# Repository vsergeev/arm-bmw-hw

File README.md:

# arm-bmw-hw

The ARM Bare Metal Widget (arm-bmw) is an open hardware Cortex-M0 development board with a focus on battery power, non-volatile storage, and debuggability. It is suitable as a battery-powered data logger or a general purpose embedded controller.

The arm-bmw features a small 70 x 43mm footprint, lithium polymer battery and USB power selection, a lithium polymer battery charger, a 2-megabyte Flash memory for data storage, a basic user interface, an FTDI-cable compatible UART header, JTAG-SWD for flashing and debugging, and 16 assorted I/O for connectivity. Its [BOM](#bill-of-materials) totals to under $15 USD. The arm-bmw is open hardware (CC-BY-4.0 licensed) and open source (MIT licensed).

Order 3 PCBs from [OSH Park](https://oshpark.com/) for $23.30 ($7.77 per board): <https://oshpark.com/shared_projects/iBdyoHro>

## Photos

## Specifications

* [NXP LPC1114FDH28](http://www.nxp.com/products/microcontrollers/cortex_m0_m0/lpc1100/LPC1114FDH28.html) 32-bit Cortex-M0 microcontroller
    * Up to 50MHz CPU
    * 12MHz on-chip RC oscillator
    * 32kB Flash, 8kB SRAM
    * 6-ch ADC, I2C, SPI, UART, PWM, Capture
* On-board 16-MBit (2-Mbyte) SPI Flash Memory (S25FL216K)
* Power
    * USB (mini-B connector) or LiPo Battery powered
    * 3-position power switch to select power between OFF, BAT, USB
    * On-board LiPo Battery Charger ([MCP73831T](http://www.microchip.com/wwwproducts/Devices.aspx?dDocName=en024903))
    * Power LED, Charge LED
* User Interface
    * On-board I2C I/O expander to save microcontroller I/Os ([MCP23008](http://www.microchip.com/wwwproducts/Devices.aspx?product=MCP23008))
    * 4 LEDs
    * 2 push buttons
    * 2 DIP switches
* Input/Output
    * 16-pin 0.1" pitch I/O header with I2C, SPI, Analog, Digital and Power pins
    * JTAG [Serial Wire Debug](http://www.arm.com/products/system-ip/debug-trace/coresight-soc-components/serial-wire-debug.php) header for Flashing and Debug
    * UART header, 6-pin [TTL-232R-3V3](http://www.ftdichip.com/Products/Cables/USBTTLSerial.htm) compatible
* Board
    * [Dangerous Prototypes SoB DP7043](http://dangerousprototypes.com/docs/Sick_of_Beige_standard_PCB_sizes_v1.0) (70x43mm / 2.756x1.693in) footprint
    * 4 mounting holes
* Miscellaneous
    * Optional external crystal and load capacitor pads
    * Hand-solderable packages

See the [datasheets](#datasheets) section below for links to part datasheets.

## Hardware Sources

Git: `git clone https://github.com/vsergeev/arm-bmw-hw.git`

GitHub: <https://github.com/vsergeev/arm-bmw-hw>

## Software Sources

Git: `git clone https://github.com/vsergeev/arm-bmw-sw.git`

GitHub: <https://github.com/vsergeev/arm-bmw-sw>

The arm-bmw-sw project includes a testing suite to verify the correct operation of the UART, SPI, I2C, SPI Flash, I/O Expander, LEDs, and Buttons.

## Details and Pinout

### Power and Charging

The arm-bmw provides a female JST-PH connector to accept a 3.7V lithium polymer battery, and a USB mini-B connector to accept 5V power from USB. The USB mini-B connector is only used for power and charging, not data.

A 3-position slide switch on the front selects between off, battery power, and USB power. The red Power LED indicates that 3.3V is present and that the arm-bmw is on. The orange Charge LED indicates that the lithium polymer battery is being charged from 5V USB power.

The onboard [MCP1252](http://www.microchip.com/wwwproducts/Devices.aspx?product=MCP1252) switched capacitor DC/DC converter regulates a 2V to 5.5V input to 3.3V, automatically switching between step down and step up operation as needed to provide 3.3V. This provides continuous power from a 3.7V lithium polymer battery as it drains to below 3.3V volts. The voltage regulator has a maximum output current of 120mA, so the arm-bmw should not be used to drive heavy loads alone.

The [MCP73831T](http://www.microchip.com/wwwproducts/Devices.aspx?dDocName=en024903) charge controller facilitates charging the connected lithium polymer battery. It operates whenever 5V power is present via the USB mini-B connector, regardless of the power slide switch state.

### Programming

The arm-bmw can be programmed and interactively debugged through its 5-pin JTAG-SWD header, with a SWD dongle like the [ST-LINK/V2](http://www.st.com/web/catalog/tools/FM146/CL1984/SC724/SS1677/PF251168?sc=internet/evalboard/product/251168.jsp). This dongle and the LPC1114 target are supported by [OpenOCD](http://openocd.sourceforge.net/). See [arm-bmw-sw](#software-sources) for configuration scripts for flashing and debugging over JTAG-SWD with openocd. See the JTAG-SWD header pinout [below](#jtag-swd-header-pinout).

The arm-bmw also supports programming over UART with its on-chip ROM bootloader. The 2-pin bootloader header on the front can be jumpered to start the on-chip ROM bootloader on reset. Software like [lpc21isp](http://sourceforge.net/projects/lpc21isp/) or [Flash Magic](http://www.flashmagictool.com/) can be used to program the LPC1114, over a UART-to-USB or UART-to-RS232 cable connected to the UART header. See the UART header pinout [below](#uart-header-pinout).

### SPI Flash Memory

The arm-bmw features a S25FL216K 16-MBit (2-MByte) SPI Flash for non-volatile storage in data logging applications. This SPI device is connected to the SPI0 controller of the microcontroller, sharing the MOSI, MISO, and SCK pins with the main [I/O header](#io-header-pinout). One microcontroller pin (`PIO0_2/SSEL0`) is dedicated to controlling its chip select.

### User Interface

The arm-bmw features a basic user interface, consisting of 4 LEDs, 2 push buttons, and 2 DIP switches. These 4 outputs and 4 inputs (8 I/Os total) are managed by an [MCP23008](http://www.microchip.com/wwwproducts/Devices.aspx?product=MCP23008) I2C I/O expander to conserve I/O pins on the microcontroller. The MCP23008 is connected to the I2C bus of the microcontroller, sharing the SDA and SCL pins with the main [I/O header](#io-header-pinout). In addition, one microcontroller pin (`PIO0_3`) is dedicated to the MCP23008 interrupt. The push buttons and DIP switches are debounced in hardware with an RC filter, to ensure that the MCP23008 interrupt is not spurious and to minimize the need for software debouncing.

The I2C address of the MCP23008 is configured by populating three 0-ohm jumpers on the back of the board, in either a 0 or 1 position, which pull down or up the MCP23008's A0, A1, A2 address pins. By default, these three jumpers are in the 0 position, so the MCP23008 has an address of `0x20` on the I2C bus.

Free software to drive the I2C bus, MCP23008 chip, and manage the UI is avaiable in the [arm-bmw-sw library](#software-sources).

### System Clock

The LPC1114 microcontroller has an on-chip 12MHz RC oscillator, which can be configured with the internal PLL to provide a 48MHz system clock using no external parts -- this is the default configuration. The arm-bmw also provides pads for an external HC49UP crystal and 0805 load capacitors for cases where a more accurate oscillator or a different multiple is required.

### I/O Header Pinout

The I/O header exposes one I2C bus (SDA, SCL), one SPI bus (MISO, MOSI, SCK), and 11 additional pins that may be used as digital I/O, ADC inputs, timer capture inputs, or PWM outputs, depending on the pin's supported functions.

| BMW Pin | uC Pin    | uC Pin Functions                  | Notes                             |
|:--------|:----------|:----------------------------------|:----------------------------------|
| `SDA`   | `PIO0_5`  | `PIO0_5/SDA`                      | I/O Expander shares this I2C bus. Pulled up with 10K. |
| `SCL`   | `PIO0_4`  | `PIO0_4/SCL`                      | I/O Expander shares this I2C bus. Pulled up with 10K. |
| `MISO`  | `PIO0_8`  | `PIO0_8/MISO0/CT16B0_MAT0`        | SPI Flash shares this SPI bus.    |
| `MOSI`  | `PIO0_9`  | `PIO0_9/MOSI0/CT16B0_MAT1`        | SPI Flash shares this SPI bus.    |
| `SCK`   | `PIO0_6`  | `PIO0_6/SCK0`                     | SPI Flash shares this SPI bus.    |
| `A0`    | `PIO0_11` | `PIO0_11/AD0/CT32B0_MAT3`         |                                   |
| `A1`    | `PIO1_0`  | `PIO1_0/AD1/CT32B1_CAP0`          |                                   |
| `A2`    | `PIO1_1`  | `PIO1_1/AD2/CT32B1_MAT0`          |                                   |
| `A3`    | `PIO1_2`  | `PIO1_2/AD3/CT32B1_MAT1`          |                                   |
| `A4`    | `PIO1_3`  | `SWDIO/PIO1_3/AD4/CT32B1_MAT2`    | JTAG-SWD header shares this pin.  |
| `A5`    | `PIO1_4`  | `PIO1_4/AD5/CT32B1_MAT3/WAKEUP`   |                                   |
| `P0`    | `PIO0_7`  | `PIO0_7/CTS`                      |                                   |
| `P1`    | `PIO0_10` | `SWCLK/PIO0_10/SCK0/CT16B0_MAT2`  | JTAG-SWD header shares this pin.  |
| `P2`    | `PIO1_5`  | `PIO1_5/RTS/CT32B0_CAP0`          |                                   |
| `P3`    | `PIO1_8`  | `PIO1_8/CT16B1_CAP0`              |                                   |
| `P4`    | `PIO1_9`  | `PIO1_9/CT16B1_MAT0`              |                                   |
| `3V3`   | -         | -                                 |                                   |
| `GND`   | -         | -                                 |                                   |

### JTAG-SWD Header Pinout

Compatible with [ST-LINK/V2](http://www.st.com/web/catalog/tools/FM146/CL1984/SC724/SS1677/PF251168?sc=internet/evalboard/product/251168.jsp) and other JTAG-SWD dongles.

| BMW Pin  | uC Pin    | uC Pin Functions                  | Notes                             |
|:---------|:----------|:----------------------------------|:----------------------------------|
| `!RST`   | `PIO0_0`  | `!RESET/PIO0_0`                   | Pulled up with 10K.               |
| `SWDIO`  | `PIO1_3`  | `SWDIO/PIO1_3/AD4/CT32B1_MAT2`    |                                   |
| `SWDCLK` | `PIO0_10` | `SWCLK/PIO0_10/SCK0/CT16B0_MAT2`  |                                   |
| `GND`    | -         | -                                 |                                   |
| `3V3`    | -         | -                                 |                                   |

### UART Header Pinout

Compatible with the [FTDI TTL-232R-3V3 cable](http://www.ftdichip.com/Products/Cables/USBTTLSerial.htm).

| BMW Pin | uC Pin   | uC Pin Functions                  | Notes                             |
|:--------|:---------|:----------------------------------|:----------------------------------|
| `GND`   | -        | -                                 |                                   |
| `NC`    | -        | -                                 |                                   |
| `NC`    | -        | -                                 |                                   |
| `uC RX` | `PIO1_6` | `PIO1_6/RXD/CT32B0_MAT0`          |                                   |
| `uC TX` | `PIO1_7` | `PIO1_7/TXD/CT32B0_MAT1`          |                                   |
| `NC`    | -        | -                                 |                                   |

## Schematic, Board, BOM

### Schematic

### Board Layout

### Bill of Materials

| Qty   | Part                                              | Description           | Part Number                       | Order Qty     | Total Price |
|:------|:--------------------------------------------------|:----------------------|:----------------------------------|:--------------|:------------|
| 1     | U1                                                | ARM Cortex-M0 MCU     | Arrow LPC1114FDH28/102:5          | 1             | 3.07        |
| 1     | U2                                                | SPI Flash Memory      | Digi-key 1274-1052-ND             | 1             | 0.32        |
| 1     | U3                                                | I2C I/O Expander      | Digi-key MCP23008-E/SO-ND         | 1             | 1.22        |
| 1     | U4                                                | 3.3V Regulator        | Digi-key MCP1252-33X50I/MS-ND     | 1             | 1.64        |
| 1     | U5                                                | LiPo Charger          | Digi-key MCP73831T-2ACI/OTCT-ND   | 1             | 0.67        |
| 8     | C3, C4, C5, C6, C10, C11, C13, C14                | C 0805 0.1uF          | Digi-key 1276-1099-1-ND           | 10            | 0.44        |
| 2     | C9, C12                                           | C 0805 1uF            | Digi-key 1276-1066-1-ND           | 5             | 0.50        |
| 2     | C15, C16                                          | C 0805 4.7uF          | Digi-key 1276-1244-1-ND           | 5             | 0.75        |
| 2     | C7, C8                                            | C 1206 10uF           | Digi-key 1276-1075-1-ND           | 5             | 1.15        |
| 8     | R1, R7, R8, R9, R14, R15, R16, R17, R18, R19, R27 | R 0805 10k            | Digi-key 1276-5332-1-ND           | 15            | 0.30        |
| 4     | R10, R11, R12, R13                                | R 0805 100k           | Digi-key 1276-3512-1-ND           | 10            | 0.20        |
| 6     | R20, R21, R22, R23, R24, R25                      | R 0603 0 jumper       | Digi-key RHM0.0CGCT-ND            | 10            | 0.10        |
| 4     | LED1, LED2, LED3, LED4                            | Green LED             | Digi-key 475-1410-1-ND            | 5             | 0.40        |
| 1     | LED_PWR                                           | Red LED               | Digi-key 475-1415-1-ND            | 2             | 0.16        |
| 1     | LED_CHG                                           | Orange LED            | Digi-key 754-1130-1-ND            | 2             | 0.40        |
| 5     | R2, R3, R4, R5, R6, R26                           | R 0805 for LED 1.5k   | Digi-key 1276-5533-1-ND           | 10            | 0.18        |
| 1     | CON_BAT                                           | JST-PH Connector      | Digi-key 455-1749-1-ND            | 1             | 0.56        |
| 1     | CON_USB                                           | USB Mini-B Connector  | Digi-key 151-1206-1-ND            | 1             | 0.41        |
| 1     | JP_*,TP_*                                         | 40p header break-away | Digi-key S1012EC-30-ND            | 1             | 0.48        |
| 1     | JP_UART                                           | 6p header right angle | Digi-key S1112EC-06-ND            | 1             | 0.23        |
| 1     | SW_PWR                                            | Slide switch          | Digi-key 563-1095-1-ND            | 1             | 0.63        |
| 2     | SW_B0, SW_B1                                      | Tactile switch        | Digi-key 450-1792-1-ND            | 2             | 0.40        |
| 1     | SW_DIP                                            | 2-pos DIP switch      | Digi-key 450-2045-ND              | 1             | 0.81        |
| 1 OPT | BATTERY                                           | 3.7V LiPo Battery     | SparkFun [PRT-00731](https://www.sparkfun.com/products/731) | 1 | 4.95 |
| 4 OPT | STANDOFF                                          | 10mm Nylon Standoff   | Digi-key 25510K-ND                | 4             | 2.36        |
| 4 OPT | STANDOFF SCREW                                    | 7mm Nylon Screw       | Digi-key 29341K-ND                | 4             | 0.76        |
| DNP   | C1, C2                                            | C 0805 xtal load caps | -                                 | -             | -           |
| DNP   | Q1                                                | Crystal               | -                                 | -             | -           |
|       | **Parts Total**                                   |                       |                                   |               | **$15.02**  |

The parts total does not include the PCB, LiPo battery, or standoffs.

Order 3 PCBs from [OSH Park](https://oshpark.com/) for $23.30 ($7.77 per board): <https://oshpark.com/shared_projects/iBdyoHro>

The unit price of a complete arm-bmw comes out to $22.79, with the BOM parts above and PCBs from OSH Park.

## Datasheets

* U1, ARM Cortex-M0 MCU, LPC1114FDH28: [site](http://www.nxp.com/products/microcontrollers/cortex_m0_m0/lpc1100/LPC1114FDH28.html), [datasheet](http://www.nxp.com/documents/data_sheet/LPC111X.pdf), [user manual](http://www.nxp.com/documents/user_manual/UM10398.pdf)
* U2, SPI Flash Memory, S25FL216K: [datasheet](http://www.spansion.com/Support/Datasheets/S25FL216K_00.pdf)
* U3, I2C I/O Expander, MCP23008: [site](http://www.microchip.com/wwwproducts/Devices.aspx?product=MCP23008), [datasheet](http://ww1.microchip.com/downloads/en/DeviceDoc/21919e.pdf)
* U4, 3.3V DC/DC Converter, MCP1252: [site](http://www.microchip.com/wwwproducts/Devices.aspx?product=MCP1252), [datasheet](http://ww1.microchip.com/downloads/en/DeviceDoc/21752B.pdf)
* U5, LiPo Charge Controller, MCP73831T: [site](http://www.microchip.com/wwwproducts/Devices.aspx?dDocName=en024903), [datasheet](http://ww1.microchip.com/downloads/en/DeviceDoc/20001984g.pdf)

## Change Log

* **Revision 2 - 06/06/2014**
    * Schematic
        * Add Dangerous Prototypes DP7043 pcb footprint and mounting holes
        * Add lipo battery charger and charge status led
        * Add mini-b usb connector for charging or usb power
        * Add capacitors for hardware debouncing for 2 pos dip switch
        * Change all 0603 size components to 0805 size
        * Change C12 size to 0805 (same as C9)
        * Change 0402 size for I2C IO expander address jumpers to 0603 size
        * Change I2C pull-ups to 10k
        * Change BL bootloader switch to a pin header jumper
        * Change test points to single pin headers
    * Layout
        * Change to longer pads on io expander
        * Change to longer pads on voltage regulator
        * Change test point pin headers to 0.1" pitch apart
        * Move passives away from I2C IO expander for easier soldering
        * Move passives away from voltage regulator for easier soldering
        * Label the UART header pins
    * BOM
        * Change power switch from mom-on-mom to on-on-on
        * Change spi flash size from 8mbit to 16mbit (same price)
        * Change to taller 2-pos DIP switch
* Revision 1 - 09/16/2013
    * Initial release

## License

arm-bmw-hw is [CC-BY-4.0](https://creativecommons.org/licenses/by/4.0/) licensed.

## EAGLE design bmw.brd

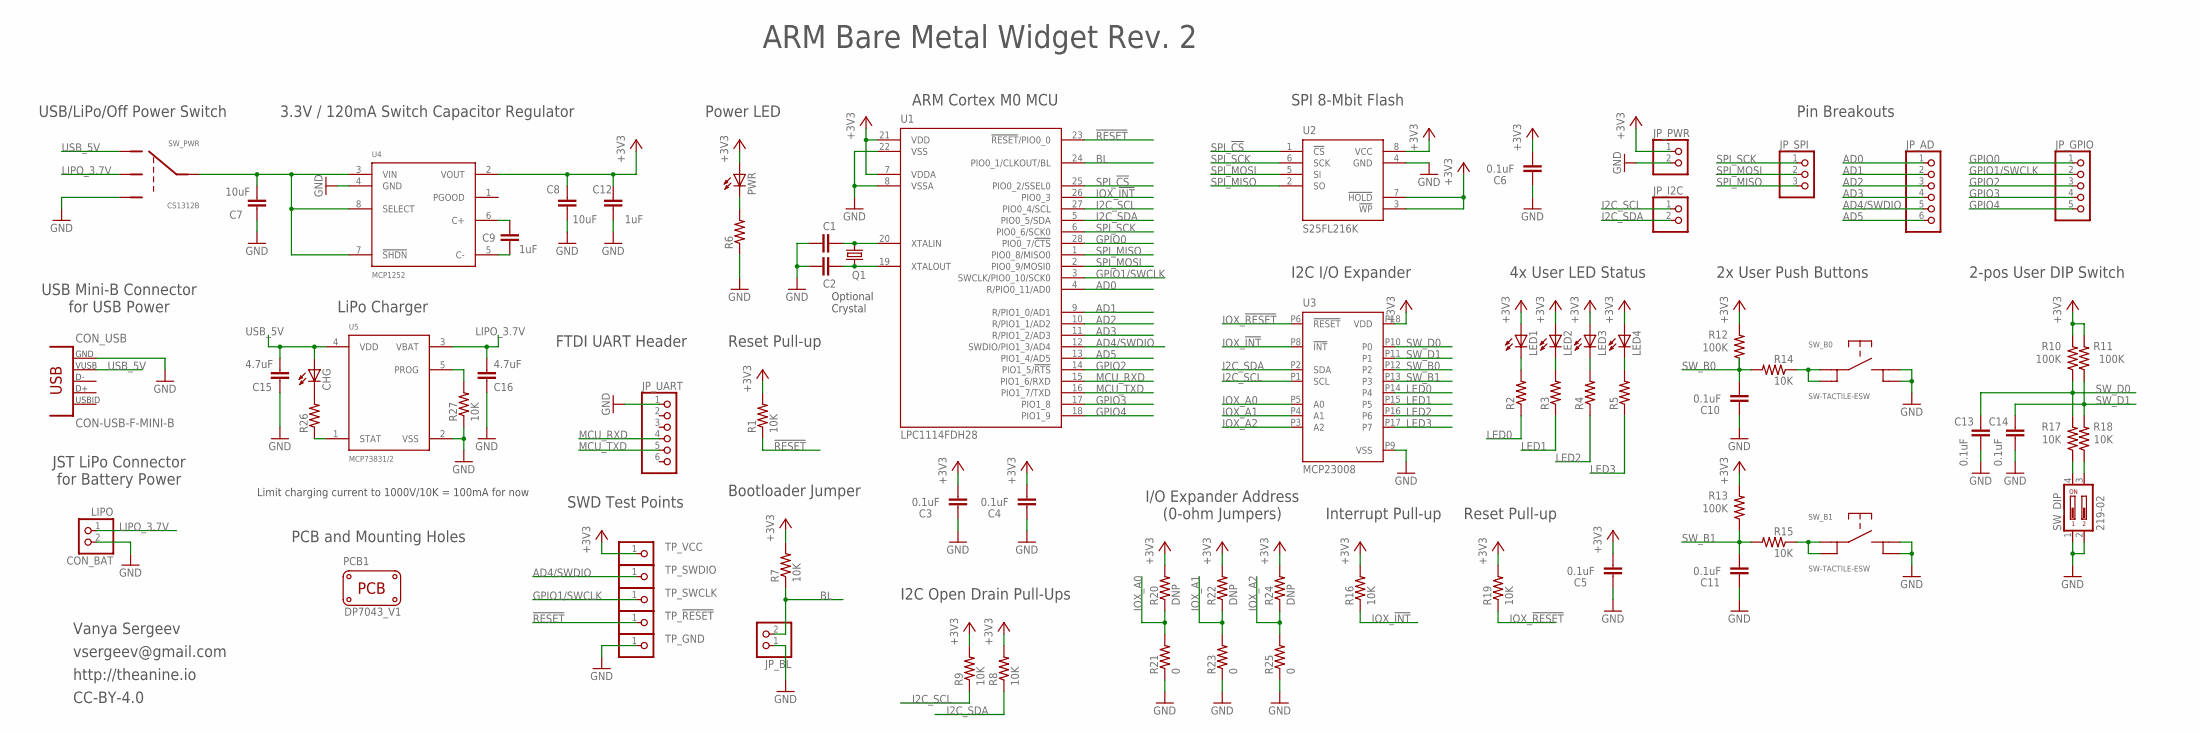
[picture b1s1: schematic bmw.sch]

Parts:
C1, C2: C-EUC0805; C0805
C3, C4, C5, C6, C10, C11, C13, C14: 0.1uF; C0805
C7, C8: 10uF; C1206
C9, C12: 1uF; C0805
C15, C16: 4.7uF; C0805
CHG: LEDCHIPLED_0805; CHIPLED_0805
CON_BAT: LIPO; JST-PH-2-SMT-RA
CON_USB: CON-USB-F-MINI-B; CONN_USB_MINI-B
JP_AD: PINHD-1X6; 1X06
JP_BL: PINHD-1X2; 1X02
JP_GPIO: PINHD-1X5; 1X05
JP_I2C: PINHD-1X2; 1X02
JP_PWR: PINHD-1X2; 1X02
JP_SPI: PINHD-1X3; 1X03
JP_UART: PINHD-1X6/90; 1X06/90
LED1, LED2, LED3, LED4: LEDCHIPLED_0805; CHIPLED_0805
PCB1: PCB_DP_RECTANGLE-43X70; DP7043_V1
PWR: LEDCHIPLED_0805; CHIPLED_0805
Q1: CRYSTALHC49UP; HC49UP
R1, R7, R8, R9, R14, R15, R16, R17, R18, R19, R27: 10K; R0805
R2, R3, R4, R5, R6, R26: R-US_R0805; R0805
R10, R11, R12, R13: 100K; R0805
R20, R22, R24: DNP; R0603
R21, R23, R25: 0; R0603
SW_B0, SW_B1: SW-TACTILE-ESW; SW-TACT-ESW
SW_DIP: 219-02; CTS-219-02
SW_PWR: CS1312B
TP_!RESET: PINHD-1X1; 1X01
TP_GND: PINHD-1X1; 1X01
TP_SWCLK: PINHD-1X1; 1X01
TP_SWDIO: PINHD-1X1; 1X01
TP_VCC: PINHD-1X1; 1X01
U1: LPC1114FDH28; TSSOP28
U2: S25FL216K; SOIC127P600X175-8N
U3: MCP23008; SOIC-18W
U4: MCP1252; MSOP8
U5: MCP73831/2; SOT23-5L

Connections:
!RESET!: R1.1, TP_!RESET.1, U1.23 (!RESET!/PIO0_0)
+3V3: C3.2, C4.2, C5.2, C6.2, C8.2, C12.2, JP_PWR.1, LED1.A, LED2.A, LED3.A, LED4.A, PWR.A, R1.2, R7.2, R8.2, R9.2, R10.2, R11.2, R12.2, R13.2, R16.2, R19.2, R20.2, R22.2, R24.2, TP_VCC.1, U1.7 (VDDA), U1.21 (VDD), U2.3 (!WP!), U2.7 (!HOLD!), U2.8 (VCC), U3.P18 (VDD), U4.2 (VOUT)
AD0: JP_AD.1, U1.4 (R/PIO0_11/AD0)
AD1: JP_AD.2, U1.9 (R/PIO1_0/AD1)
AD2: JP_AD.3, U1.10 (R/PIO1_1/AD2)
AD3: JP_AD.4, U1.11 (R/PIO1_2/AD3)
AD4/SWDIO: JP_AD.5, TP_SWDIO.1, U1.12 (SWDIO/PIO1_3/AD4)
AD5: JP_AD.6, U1.13 (PIO1_4/AD5)
BL: JP_BL.2, R7.1, U1.24 (PIO0_1/CLKOUT/BL)
GND: C1.1, C2.1, C3.1, C4.1, C5.1, C6.1, C7.1, C8.1, C10.1, C11.1, C12.1, C13.2, C14.2, C15.1, C16.1, CON_BAT.2 (1), CON_USB.GND, JP_BL.1, JP_PWR.2, JP_UART.1, R6.1, R21.1, R23.1, R25.1, R27.1, SW_B0.P3, SW_B0.P4, SW_B1.P3, SW_B1.P4, SW_DIP.1, SW_DIP.2, SW_PWR.P4 (3), TP_GND.1, U1.8 (VSSA), U1.22 (VSS), U2.4 (GND), U3.P9 (VSS), U4.4 (GND), U5.2 (VSS)
GPIO0: JP_GPIO.1, U1.28 (PIO0_7/!CTS!)
GPIO1/SWCLK: JP_GPIO.2, TP_SWCLK.1, U1.3 (SWCLK/PIO0_10/SCK0)
GPIO2: JP_GPIO.3, U1.14 (PIO1_5/!RTS!)
GPIO3: JP_GPIO.4, U1.17 (PIO1_8)
GPIO4: JP_GPIO.5, U1.18 (PIO1_9)
I2C_SCL: JP_I2C.1, R9.1, U1.27 (PIO0_4/SCL), U3.P1 (SCL)
I2C_SDA: JP_I2C.2, R8.1, U1.5 (PIO0_5/SDA), U3.P2 (SDA)
IOX_!INT: R16.1, U1.26 (PIO0_3), U3.P8 (!INT)
IOX_!RESET: R19.1, U3.P6 (!RESET)
IOX_A0: R20.1, R21.2, U3.P5 (A0)
IOX_A1: R22.1, R23.2, U3.P4 (A1)
IOX_A2: R24.1, R25.2, U3.P3 (A2)
LED0: R2.1, U3.P14 (P4)
LED1: R3.1, U3.P15 (P5)
LED2: R4.1, U3.P16 (P6)
LED3: R5.1, U3.P17 (P7)
LIPO_3.7V: C16.2, CON_BAT.1 (2), SW_PWR.P2 (2), U5.3 (VBAT)
MCU_RXD: JP_UART.4, U1.15 (PIO1_6/RXD)
MCU_TXD: JP_UART.5, U1.16 (PIO1_7/TXD)
unnamed: R17.1, SW_DIP.4
unnamed: C1.2, Q1.2, U1.20 (XTALIN)
unnamed: C2.2, Q1.1, U1.19 (XTALOUT)
unnamed: PWR.C, R6.2
unnamed: C7.2, SW_PWR.P3 (C), U4.3 (VIN), U4.7 (!SHDN), U4.8 (SELECT)
unnamed: C9.2, U4.6 (C+)
unnamed: C9.1, U4.5 (C-)
unnamed: LED1.C, R2.2
unnamed: LED2.C, R3.2
unnamed: LED3.C, R4.2
unnamed: LED4.C, R5.2
unnamed: R14.1, SW_B0.P1, SW_B0.P2
unnamed: R15.1, SW_B1.P1, SW_B1.P2
unnamed: R18.1, SW_DIP.3
unnamed: CHG.C, R26.2
unnamed: R26.1, U5.1 (STAT)
unnamed: R27.2, U5.5 (PROG)
SPI_!CS!: U1.25 (PIO0_2/SSEL0), U2.1 (!CS!)
SPI_MISO: JP_SPI.3, U1.1 (PIO0_8/MISO0), U2.2 (SO)
SPI_MOSI: JP_SPI.2, U1.2 (PIO0_9/MOSI0), U2.5 (SI)
SPI_SCK: JP_SPI.1, U1.6 (PIO0_6/SCK0), U2.6 (SCK)
SW_B0: C10.2, R12.1, R14.2, U3.P12 (P2)
SW_B1: C11.2, R13.1, R15.2, U3.P13 (P3)
SW_D0: C13.1, R10.1, R17.2, U3.P10 (P0)
SW_D1: C14.1, R11.1, R18.2, U3.P11 (P1)
USB_5V: C15.2, CHG.A, CON_USB.VUSB, SW_PWR.P1 (1), U5.4 (VDD)

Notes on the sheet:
I2C I/O Expander
SPI 8-Mbit Flash
ARM Cortex M0 MCU
Reset Pull-up
4x User LED Status
2x User Push Buttons
2-pos User DIP Switch
SWD Test Points
FTDI UART Header
Bootloader Jumper
Power LED
I2C Open Drain Pull-Ups
3.3V / 120mA Switch Capacitor Regulator
USB/LiPo/Off Power Switch
ARM Bare Metal Widget Rev. 2
Vanya Sergeev
vsergeev@gmail.com
http://theanine.io
Pin Breakouts
Optional Crystal
Interrupt Pull-up
I/O Expander Address (0-ohm Jumpers)
PCB and Mounting Holes
LiPo Charger
Limit charging current to 1000V/10K = 100mA for now
USB Mini-B Connector for USB Power
JST LiPo Connector for Battery Power
CC-BY-4.0

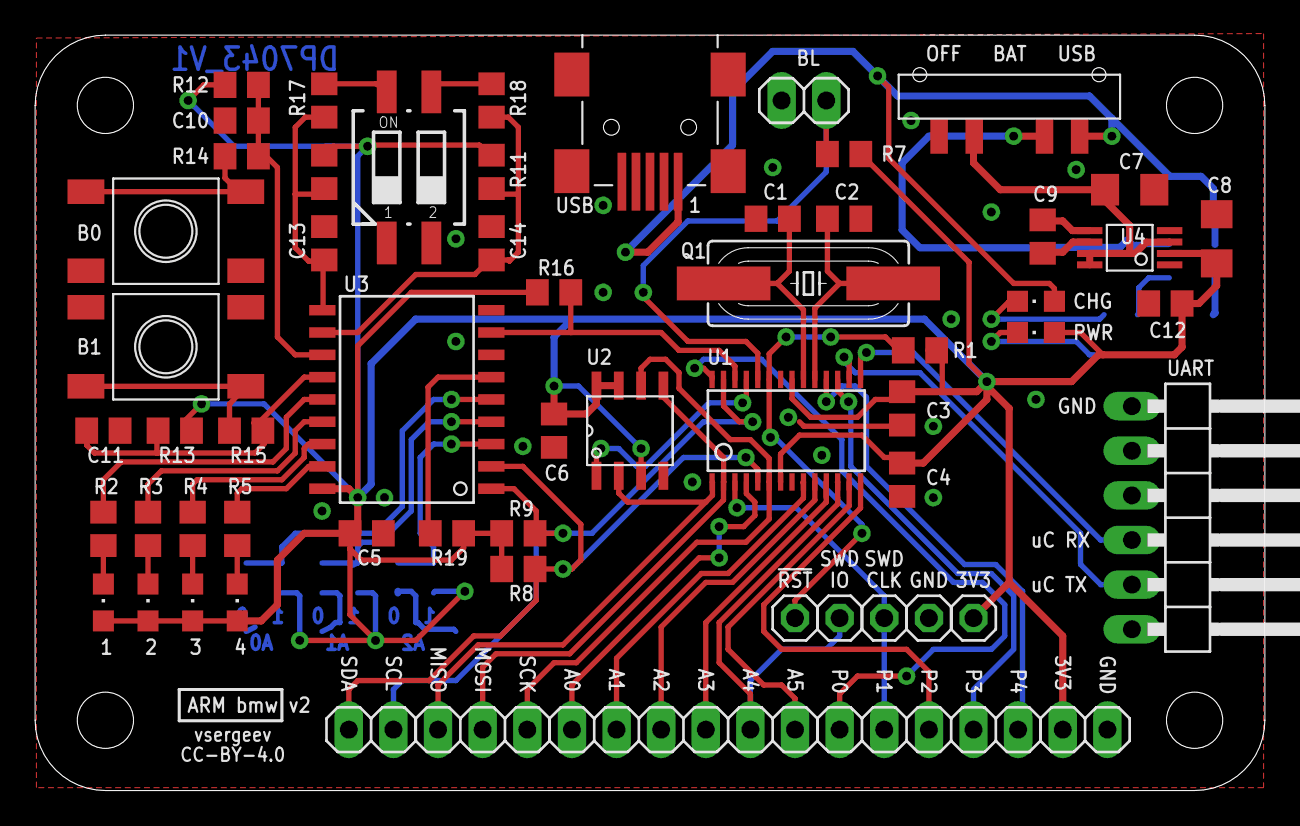
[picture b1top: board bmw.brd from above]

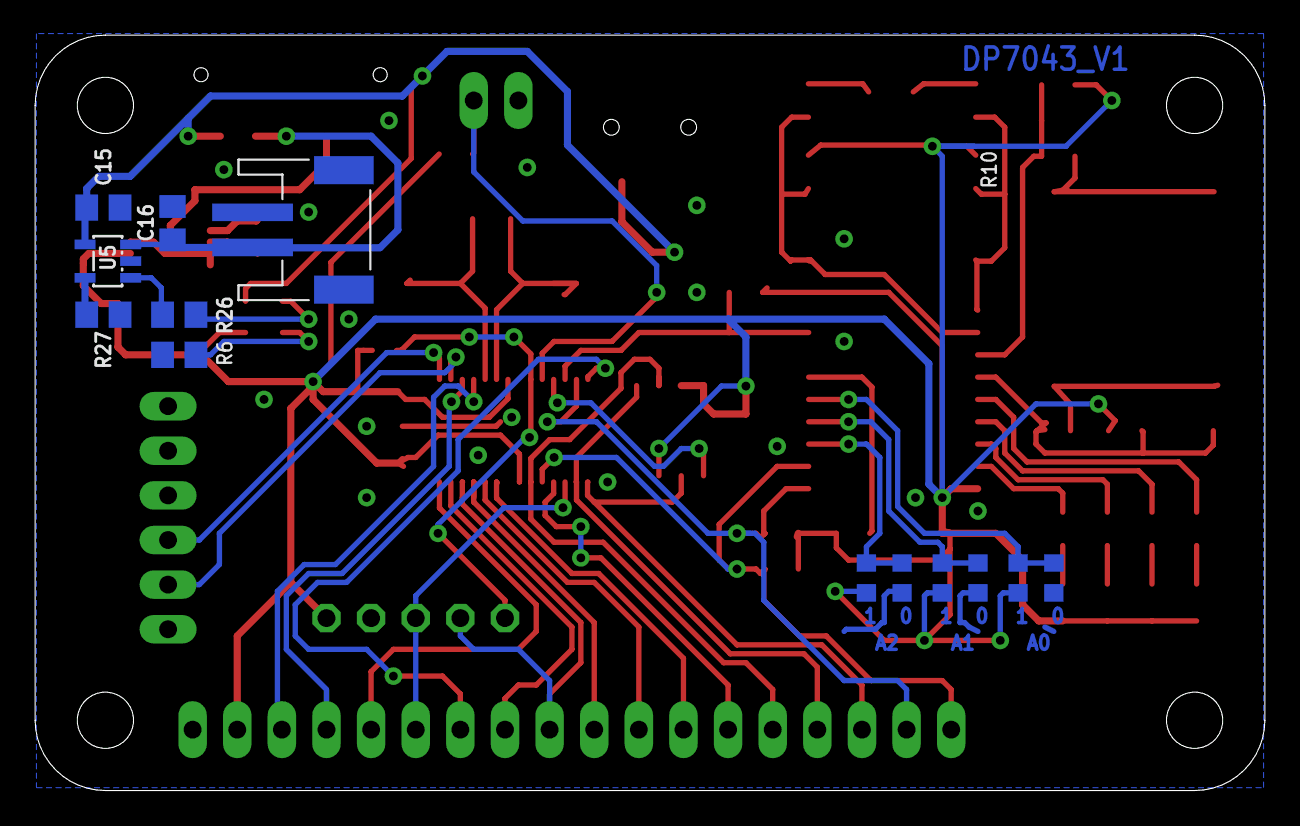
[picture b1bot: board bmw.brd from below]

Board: 2 copper layers, 70.0 x 43.0 mm, 74 parts (13 on the bottom side), 55 nets.

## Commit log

2014-06-09 initial commit with revision 1
2014-06-09 revision 2
2014-07-25 add changelog
2014-07-25 add misc/ to gitignore
2014-07-25 fix spi flash value in schematic
2014-07-25 add README
2014-07-25 minor fixes to README
2014-07-25 add bootloader header to breakdown image
2014-07-25 minor formatting fixes on readme
2014-08-06 move up software sources section in README
2014-08-07 move sources section down in README
2014-10-13 add OSH Park link and update BOM in README
2014-10-13 minor clarifications to board details in README
2017-04-25 remove old git remote from README

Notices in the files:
README.md:
arm-bmw-hw is [CC-BY-4.0](https://creativecommons.org/licenses/by/4.0/) licensed.
